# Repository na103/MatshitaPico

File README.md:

<!--
  MatshitaPico — Solid-state CD-ROM drive replacement for the Commodore CDTV
  Copyright (c) 2026 Nicola Avanzi (na103)
  Licensed under Creative Commons Attribution 4.0 International (CC BY 4.0).
  See LICENSE.
-->

# MatshitaPico — a solid-state CD-ROM drive for the Commodore CDTV

**MatshitaPico** is a solid-state replacement for the optical CD-ROM drive of the
**Commodore CDTV**: BIN/CUE disc images stored on a microSD
card take the place of the optical mechanism.

**Why:** many CDTV drives have a worn-out laser and cannot be repaired, and no drop-in
replacement has ever existed. This project keeps these machines alive.

> This repository contains the **CPLD design (HDL)**, **technical documentation**, **RP2350 firmware**, **KiCad hardware project of beta board** and the **Amiga-side `mpdisk.device` + boot CD builder** for hardfiles.
---

## Community beta

Because of the limited turnout in the project's closed beta testing, I have decided to open
MatshitaPico testing up to the whole Amiga community.

The final version should not differ much from this first one, apart from an ATF1508 CPLD in a
TQFP-100 package, programmable in-circuit through a JTAG connector. The key point for the final
version is the **PCB layout**: it must be designed together with a 3D-printed mounting bracket.
The original eject button could also be reused as a control button.

This first version **is** installable — as you can see from the photos [here](https://github.com/na103/MatshitaPico/tree/main/img/beta_assembly) —
but several modifications are needed to fit it. When I laid out the PCB I did not worry about
its dimensions.

## The key insight

The CDTV service manual contains **no schematic for the CD-ROM subsystem**: all of the
CD-ROM electronics (CD-DSP, the Sanyo **LC8951** decoder, the drive's own microcontroller)
live on a PCB **inside the drive mechanism**, not on the motherboard. The motherboard only
carries the *host side* — the **DMAC (U36)**, the **6525/TPI (U32)** and glue logic — which
talks to the drive through connector **CN9** (42 pins, sheet 10 of schematic #252605).

→ **CN9 is the emulation point.** The device plugs into CN9 and pretends to be the entire
drive. The LC8951 does **not** interpret commands (it is a host↔µC FIFO mailbox); the
replacement emulates both the LC8951 host interface and the drive µC command protocol
(the proprietary CDTV/Sony command set).

## Hardware architecture

```
   CDTV (CN9, 5 V TTL)
        |  DB0-7, _HWR/_HRD/_CMD/_STEN/_DTEN/DRQ/_ENABLE/_STCH + RESET
        v
   CPLD  ATF1508AS  (5 V, 128 macrocells, PLCC84, JTAG; socketed, programmed out of circuit)
        |  - real-time 5 V front-end; host-interface FSM (DRQ mode)
        |  - clock division C16M -> BCLK/LRCK; SCOR / subcode generation
        |  <- level shifting 5 V <-> 3.3 V (SN74CBTD16211 bus switch, no DIR, 5 V clamp)
        v
   MCU  RP2350 / Raspberry Pi Pico 2  (3.3 V)
        - drive command protocol - BIN/CUE from SD
        - I2S audio 44.1 kHz (PIO) - subcode Q - UI (NEXT + LED)
   + 16.9344 MHz crystal oscillator (C16M, DIP14 metal-can 5 V TTL)
```

**Key constraint:** the CN9 bus is 5 V TTL and the RP2350 is **not** 5 V-tolerant, so a
native 5 V front-end is required (**ATF1508AS**, the `AS` variant, not `ASV`). The CPLD
performs four things in parallel — master clock, I2S audio, subcode, host DMA — plus command
glue logic; the heavy protocol logic runs on the RP2350.

## What the CPLD does

The CPLD is the only chip that faces CN9 (a pure 5 V domain). It contains:

- **`clkgen`** — derives the audio clocks (`BCLK`, `LRCK`, frame sync) from the `C16M`
  master clock (16.9344 MHz = 384 x 44.1 kHz), so the audio stays phase-coherent with the
  motherboard DAC (Sanyo LC7883M).
- **`host_if`** — the LC8951-style host-interface FSM: it captures host commands (async latch
  on the rising edge of `_HWR`), drives status replies over `_HRD`/`_STEN`, and runs the DMA
  data path in **DRQ mode** (`DRQ` high = byte ready). `EOP` is not on CN9 — the DMAC counts
  it — so ending a sector is just lowering `DRQ`.
- **top level** — subcode generation (`SBCP`/`SCOR`/`EFFK`; `SCCK` is a host **input**) and
  buffering of `DATA`/`EMPHASIS` from the RP2350.

## The golden reference

`cdtv.cpp` from WinUAE (plus `cdtvcr.cpp` for the CDTV-CR variant) is a complete emulation of
the DMAC + 6525 + LC8951 + command protocol. It is the **executable specification** the
firmware is ported from. (The WinUAE sources are not redistributed here — see the WinUAE
project.) The CDTV extended ROM is the real host-side protocol engine.

## Drive command set (summary)

`0x01` seek · `0x02` read · `0x04`/`0x05` motor on/off · `0x09`/`0x0a` play LSN/MSF ·
`0x0b` play track range · `0x82` clear-error · `0x84` mode set · `0x85` mode sense ·
`0x86` capacity · `0x87` subq · `0x8a` read TOC · `0xa2`/`0xa3` front panel.

The full, byte-level command reference — including the vendor `0x6x` hardfile page — is in
[`docs/drive-commands.md`](docs/drive-commands.md).

## Status

The device is functionally complete on real hardware: data boot, persistent disc change,
CD audio (play / pause / skip / stop), CD+G graphics, and the activity LED all work on a real
CDTV. 

## Optional: hardfiles (`mpdisk.device`)

With the firmware built with `ENABLE_MPDISK`, `.hdf` hard-disk images in the root of the SD
card become read/write Amiga units **MPD0..MPD3**, served through the CD controller itself
(no extra hardware). A small boot CD loads `mpdisk.device`, mounts the hardfiles and hands the
system over to MPD0:, so a CDTV can run Workbench from a writable disk. The Amiga sources and
the boot CD builder are in [`amiga/`](amiga) and [`tools/`](tools) — see
[`amiga/README.md`](amiga/README.md).

## Thanks
Thankyou to all the people who have support this project.<br>
Andrea Quagliarini, Mirco Gaggiottini, Carlo Santagostino, Federico Di Dato.

## License

This work is licensed under the **Creative Commons Attribution 4.0 International License
(CC BY 4.0)**. See [`LICENSE`](LICENSE). You are free to share and adapt the material for any
purpose, provided you give appropriate credit.

<br><br>
If you found this my work useful, please consider buying me a cup of coffee if you want:<br>

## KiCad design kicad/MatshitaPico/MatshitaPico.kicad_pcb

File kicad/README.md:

## Bill of materials
| Qt. |    Description     |             Designator          |    Part code       |             Note              |
|:---:|--------------------|---------------------------------|--------------------|-------------------------------|
|4    |Res 10K             |R1-R3,R22                        |RC1206FR-0710KL
|6    |Res 100R            |R15,R17-R21                      |RC1206FR-07100RL    |                               |
|8    |Res 47K             |R4-R11                           |RC1206FR-0747KL     |                               |
|2    |Res 470R            |R12, R13                         |RC1206FR-07470RL    |                               |
|2    |Res 1K              |R14,R16                          |RC1206FR-071KL      |                               |
|1    |Res 0R              |R23                              |RC1206FR-070RL      |                               |
|1    |Bus Array 8RES 2.2K |RN1                              |4609X-101-222LF     |                               |
|1    |Bus Array 4RES 1K   |RN2                              |4605X-101-102LF     |                               |
|17   |Cap 100nF           |C1-C13,C17-C20                   |C1206C104K5RACTU    |                               |
|2    |Cap 10uF            |C15,C16                          |EEA-GA1V100H        |                               |
|1    |Cap 47uF            |C14                              |EEU-FC1V470H        |                               |
|1    |DIODE SCHOTTKY      |D1                               |MBR120ESFT3G        |                               |
|1    |DIODE SCHOTTKY      |D2                               |BAT54W-E3-08        |                               |
|1    |BUS SWITCH          |U2                               |SN74CBTD16211DGGR   |                               |
|1    |CPLD ATF1508        |U1                               |ATF1508AS-10JU84    | from ebay or utsource.net     |
|1    |OSC DIP 16.9344MHZ  |Y1                               |NA                  | from aliexpress               | 
|1    |74LS245             |U3                               |SN74LS245DWR        |                               |
|2    |74LS244             |U4,U6                            |SN74LS244DWR        |                               |
|1    |74LS541             |U5                               |SN74LS541DWR        |                               | 
|1    |SOCKET PLCC 84POS   |U1                               |940-44-084-24-000000|                               |
|1    |PI PICO 2 RP2350    |A1                               |SC1631              |                               |
|1    |CONN 4POS 5.08MM    |J1                               |641737-1            |                               |
|1    |CONN 40POS 2.54MM   |J2                               |61204021721         |                               |
|1    |CONN 3POS 2MM       |J3                               |S3B-PH-K-S          |                               |
|1    |CONN SD CARD SMD    |SD1                              |10067847-011RLF     |                               |
|1    |SWITCH SPST-NO      |SW1                              |2-1825027-0         |                               |

## Note ##
The ATF150x programmer needed to program the CPLD can be found [here](https://github.com/roscopeco/atfprog-hardware).

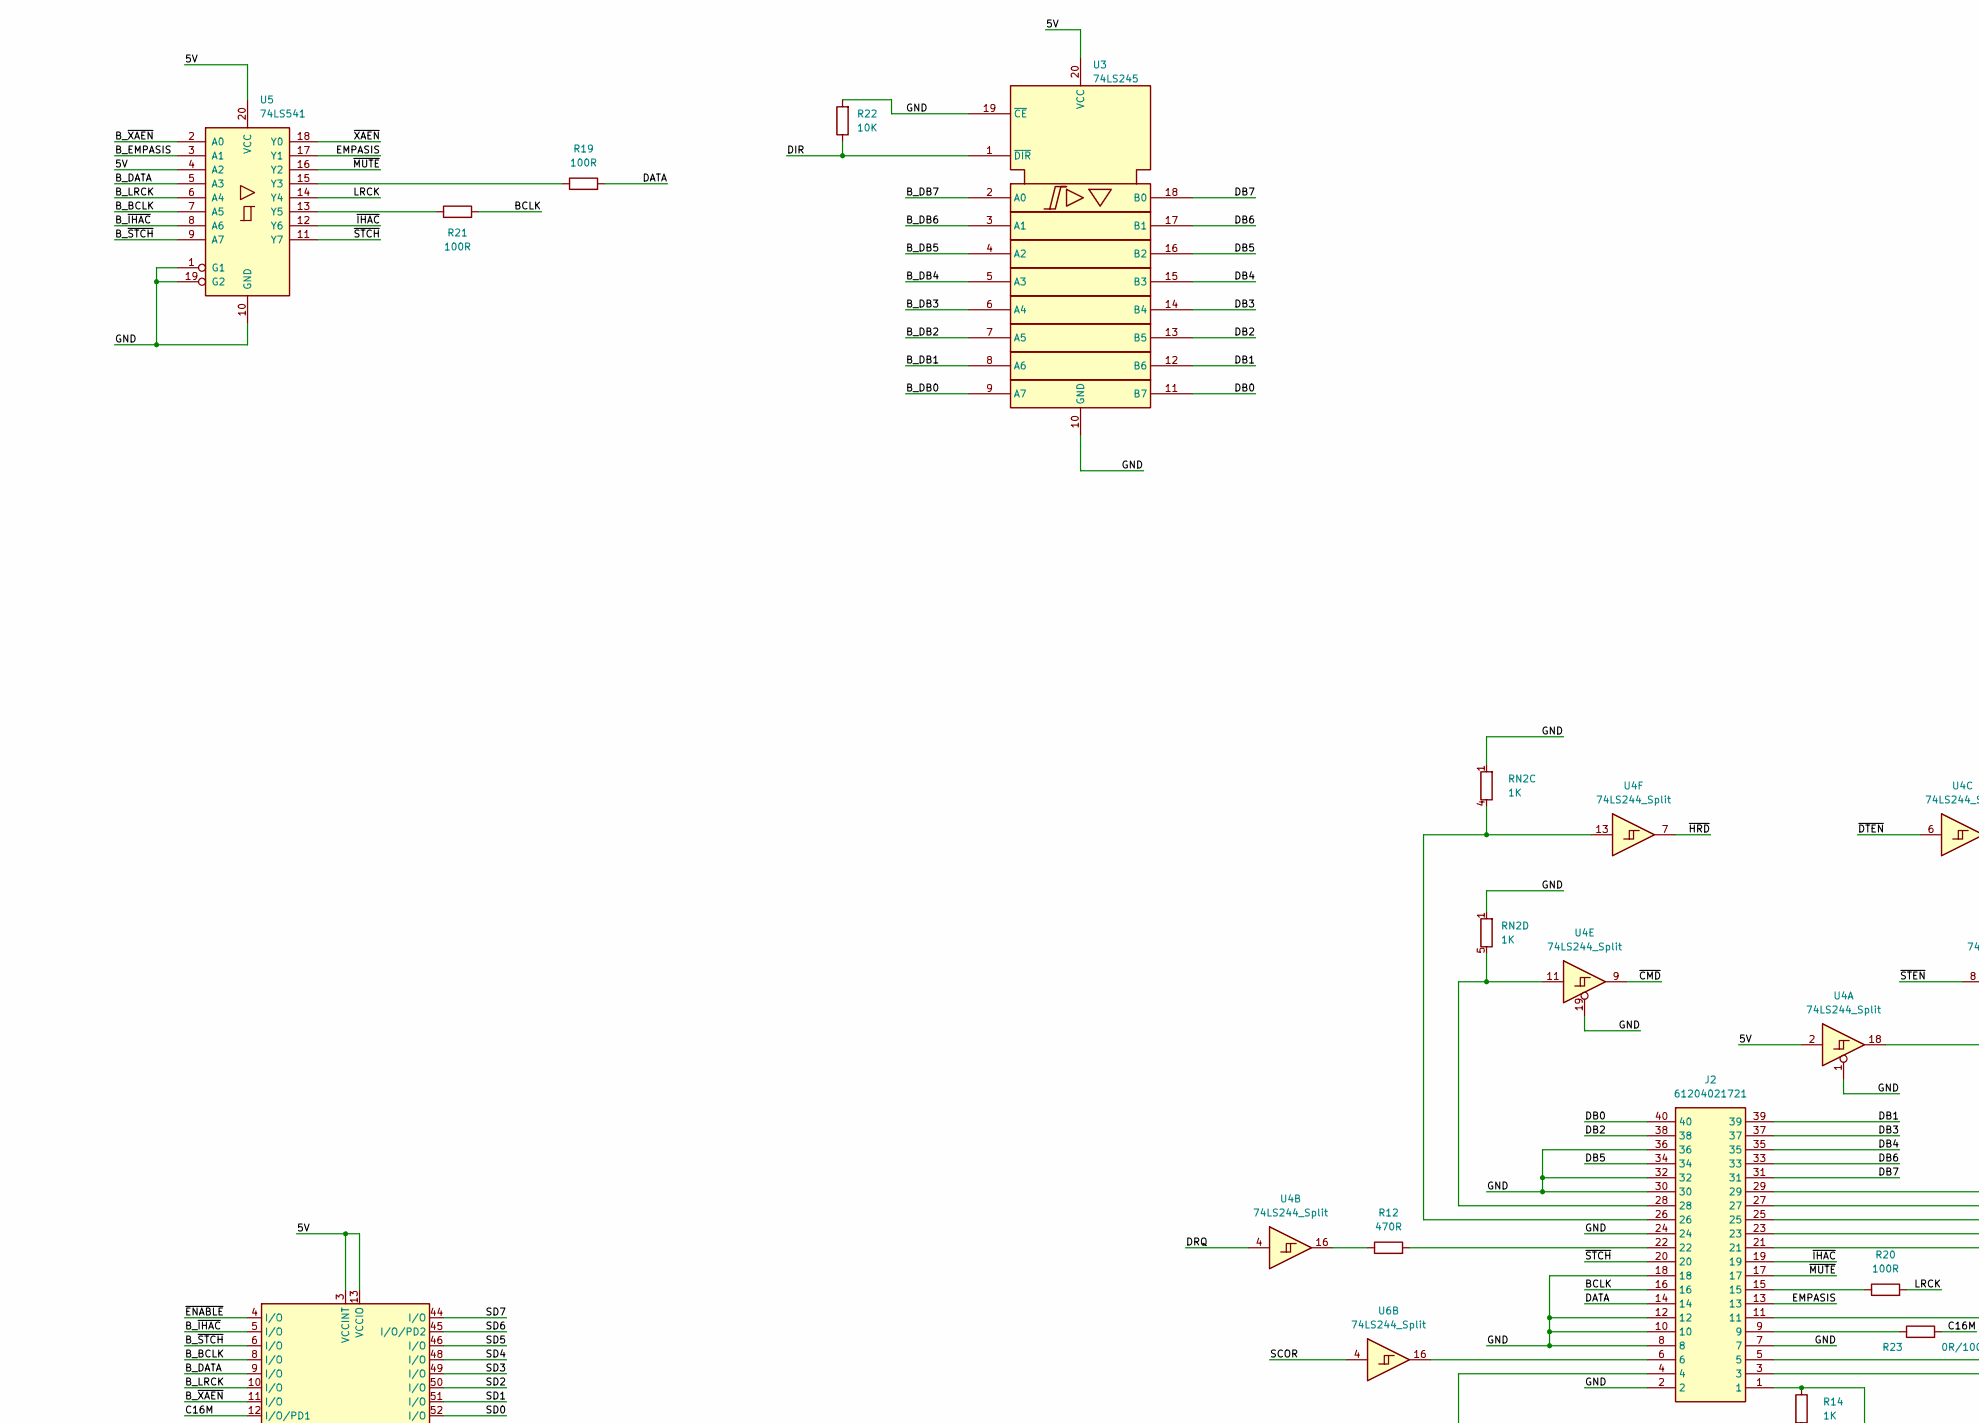
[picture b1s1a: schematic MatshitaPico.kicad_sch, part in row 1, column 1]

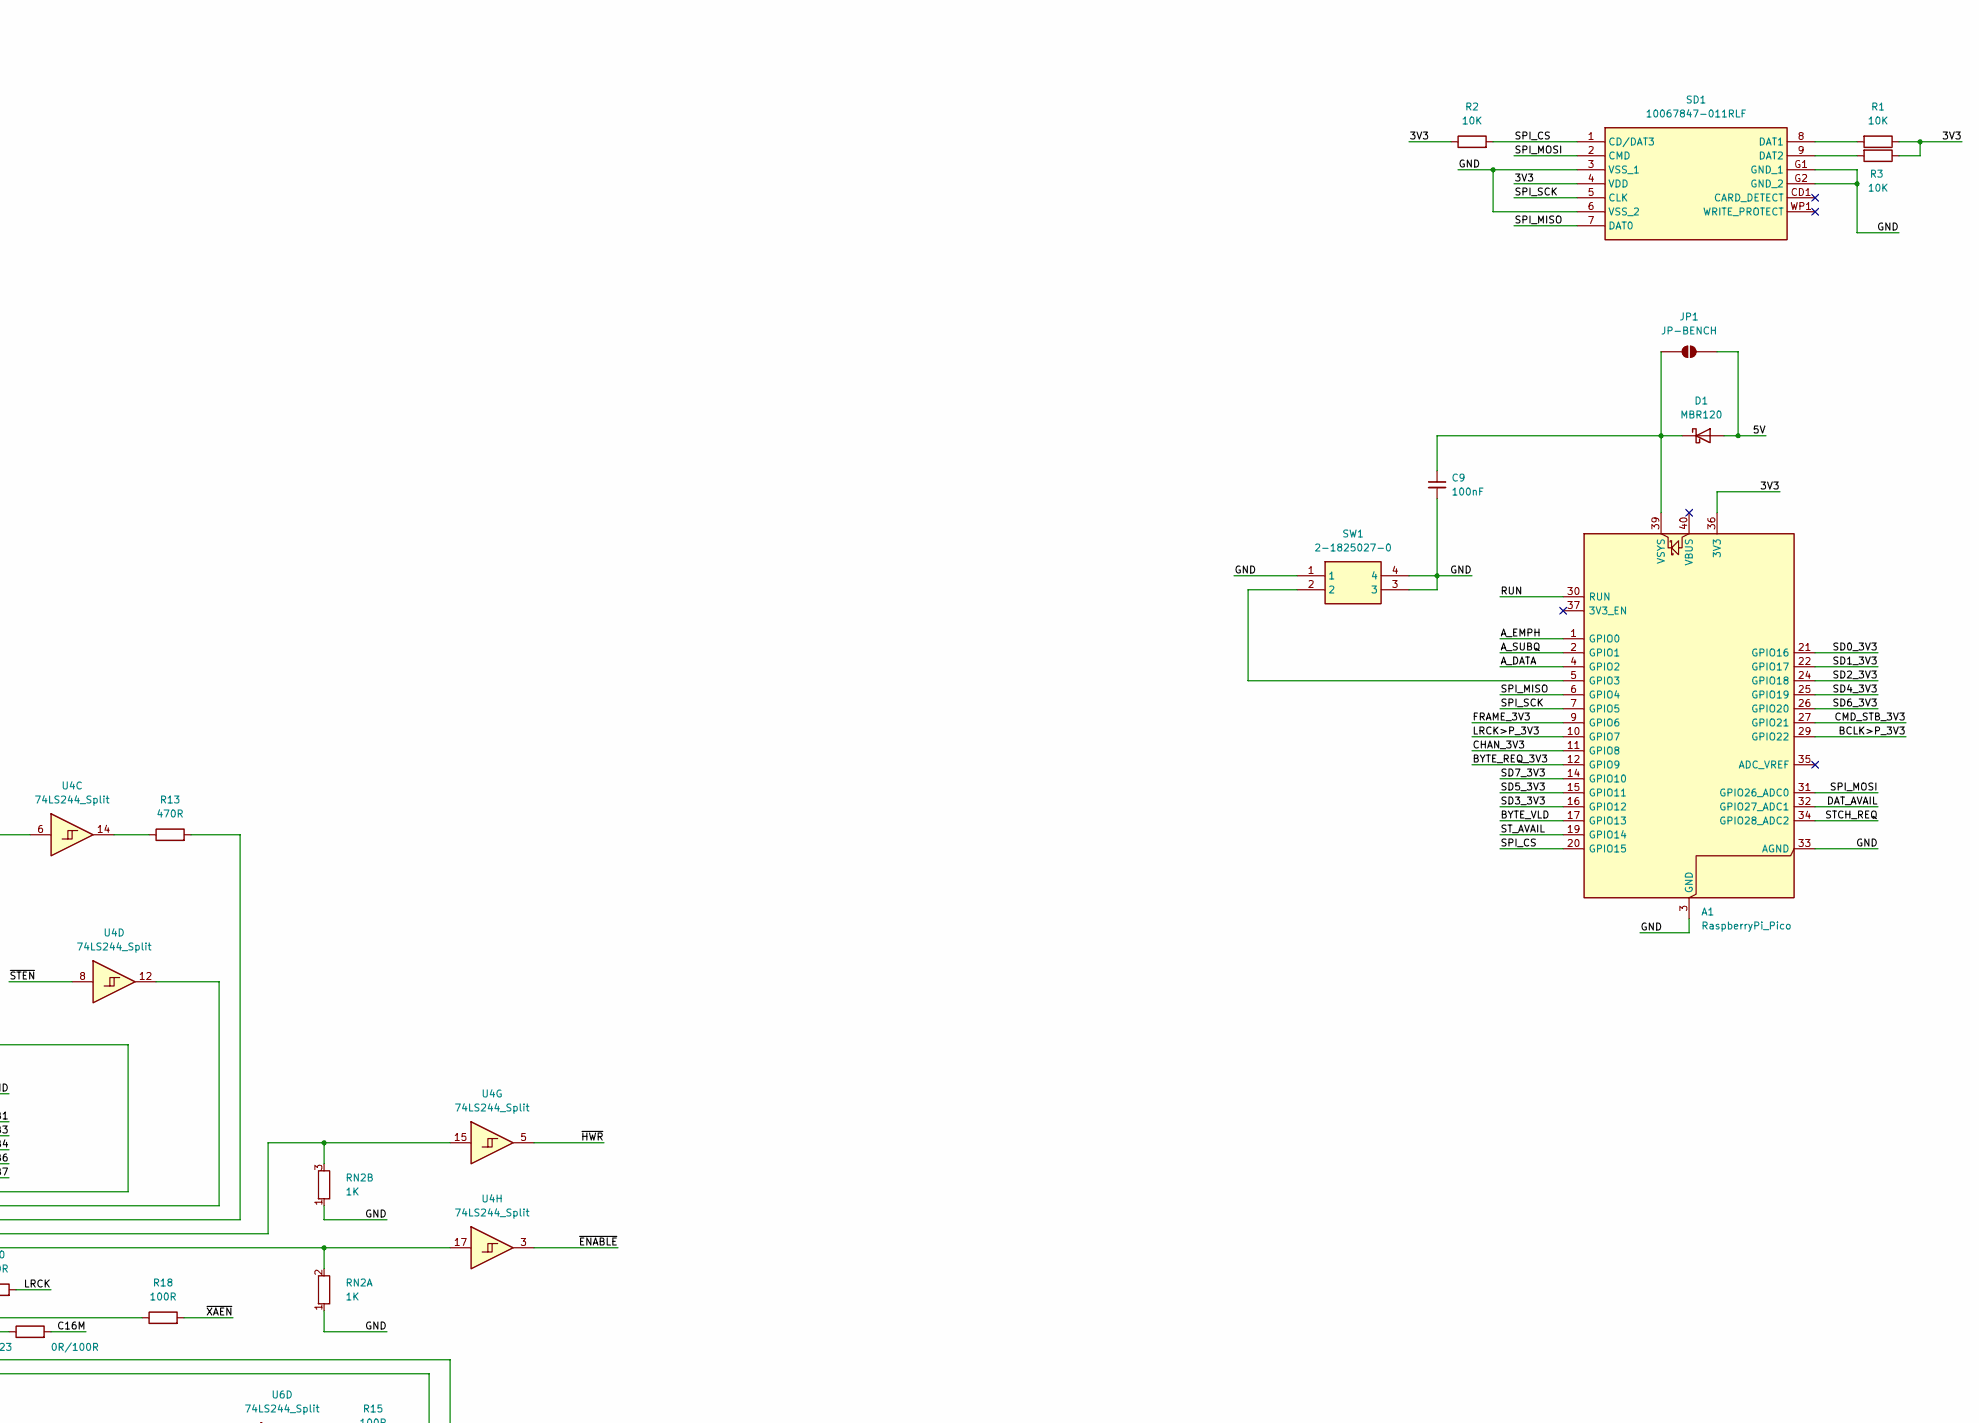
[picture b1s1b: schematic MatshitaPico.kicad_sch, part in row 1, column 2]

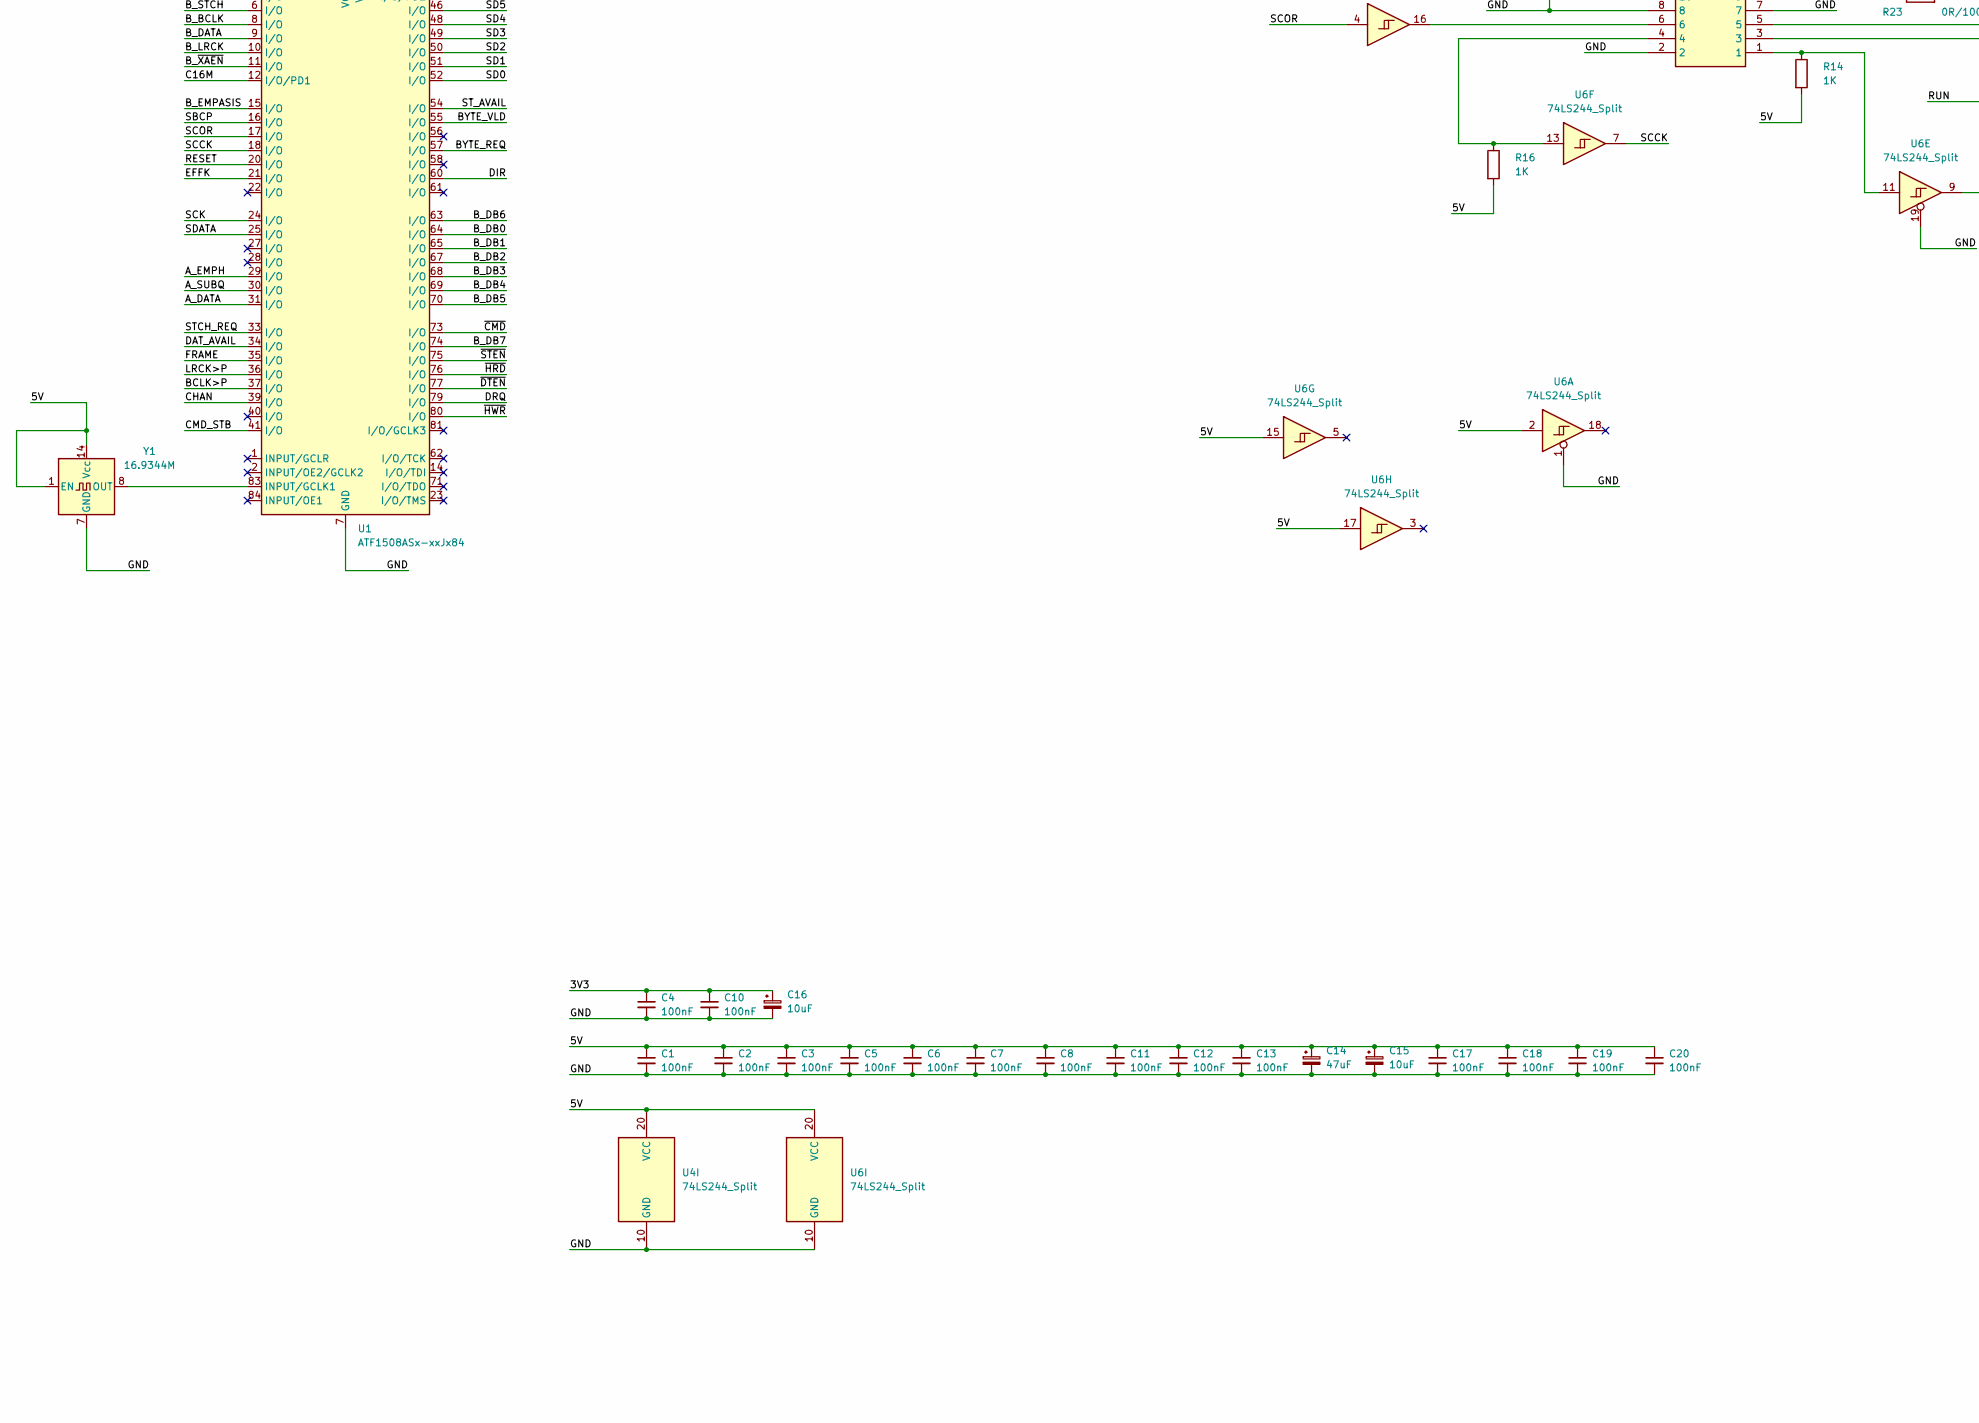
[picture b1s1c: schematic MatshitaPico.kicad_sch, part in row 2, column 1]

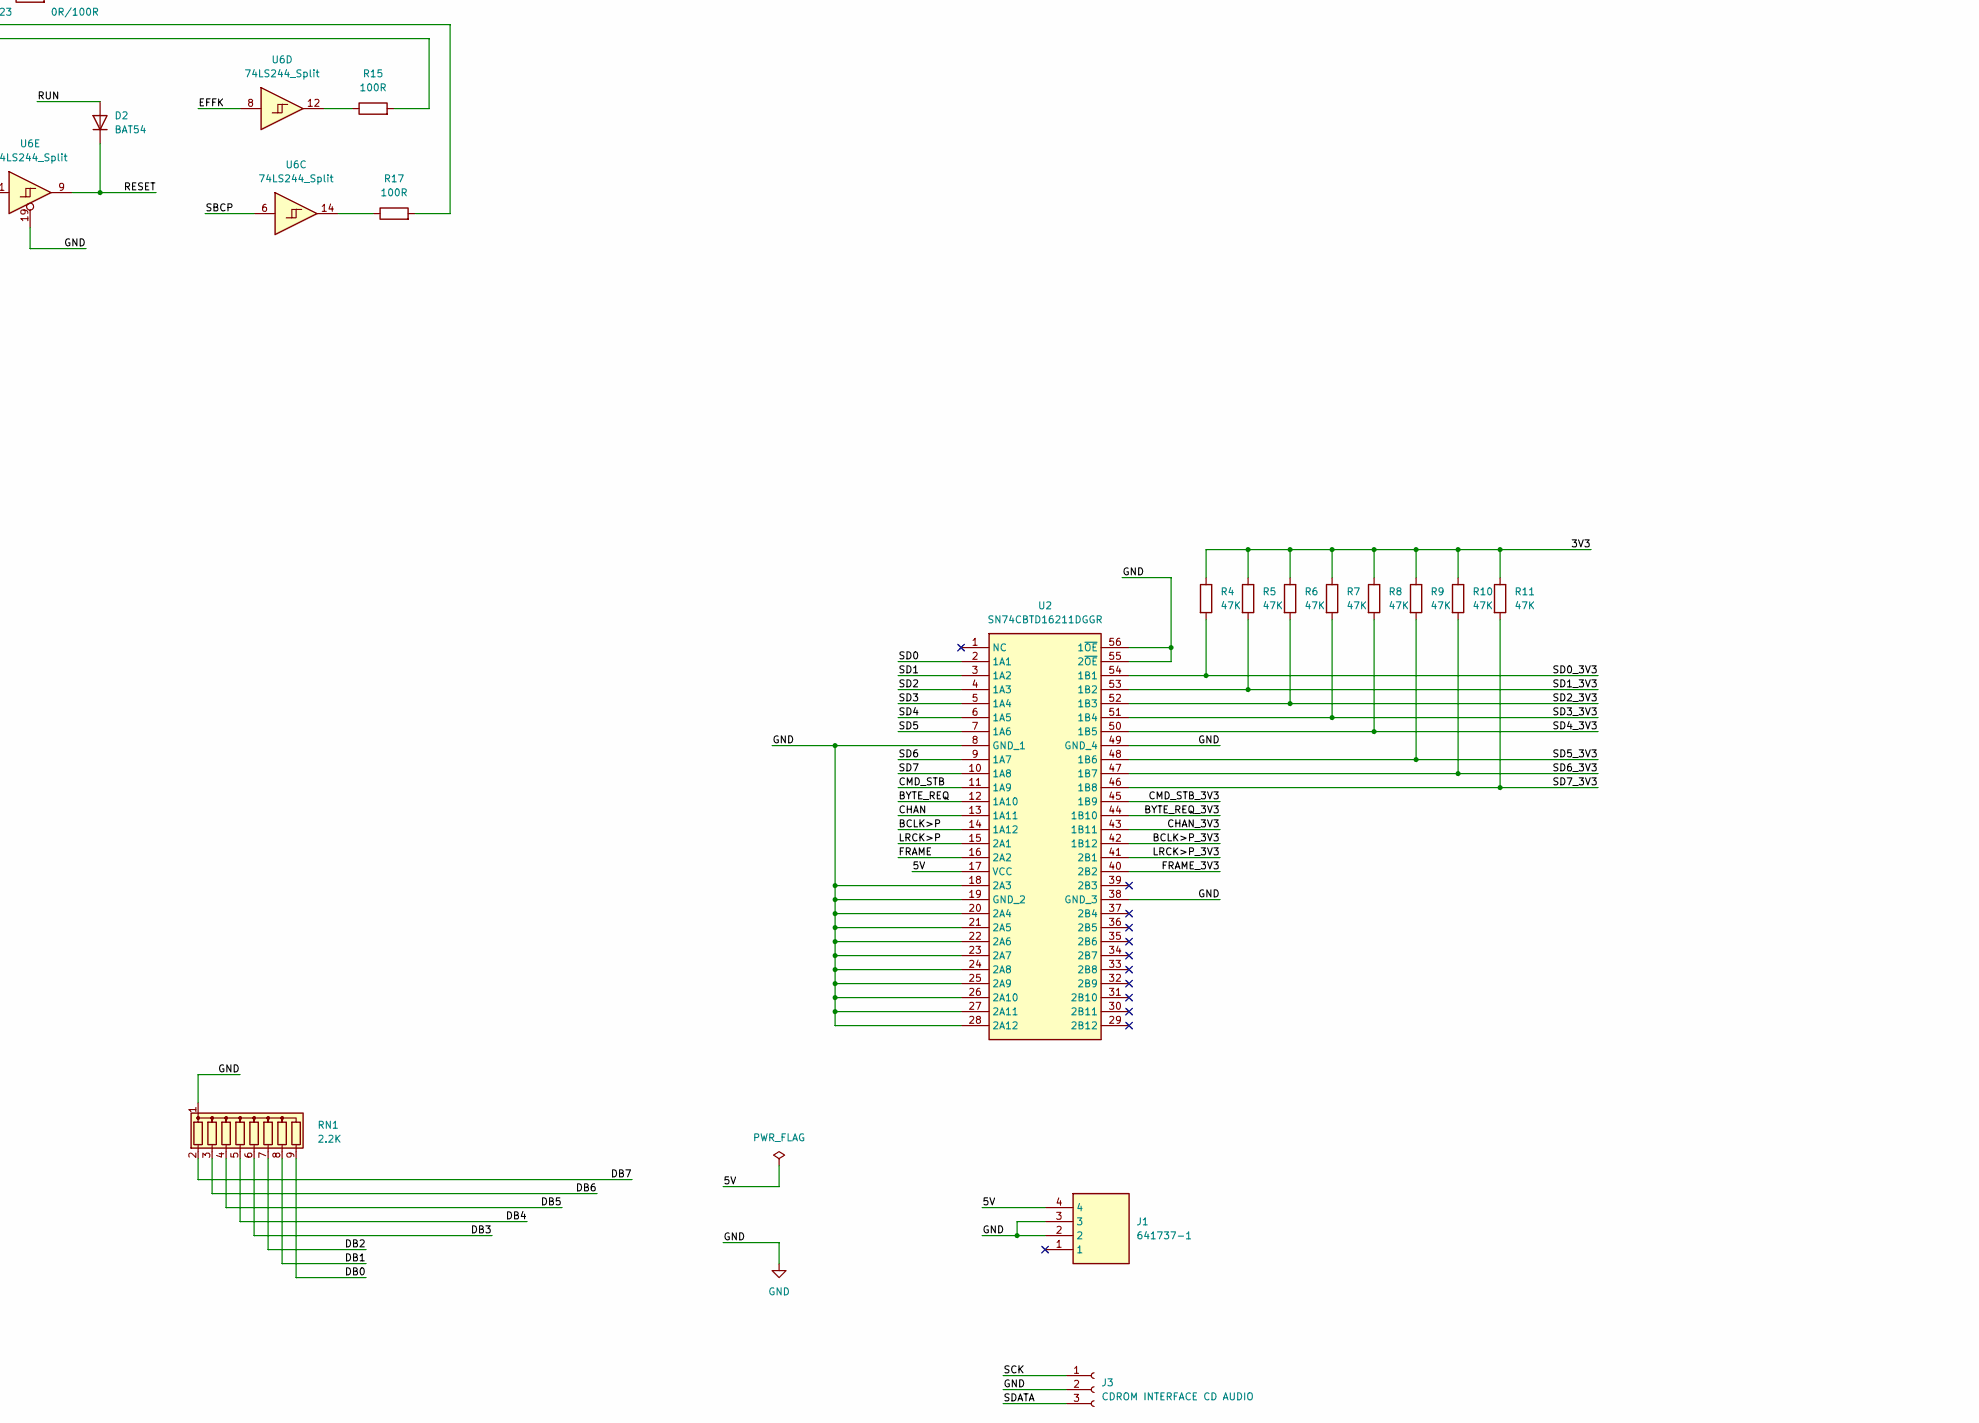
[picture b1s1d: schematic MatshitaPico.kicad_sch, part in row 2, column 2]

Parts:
A1: RaspberryPi_Pico; RaspberryPi_Pico_Common_no_wifi
C1, C2, C3, C4, C5, C6, C7, C8, C9, C10, C11, C12, C13, C17, C18, C19, C20: 100nF; C_1206_3216Metric_Pad1.33x1.80mm_HandSolder
C14: 47uF; CP_Radial_D5.0mm_P2.50mm
C15, C16: 10uF; CP_Radial_D5.0mm_P2.50mm
D1: MBR120; SODFL3616X98N
D2: BAT54; SODFL3616X98N
J1: 641737-1; Mouser Part Number 571-6417371
J2: 61204021721; Mouser Part Number 710-61204021721
J3: CDROM INTERFACE CD AUDIO; JST_PH_S3B-PH-K_1x03_P2.00mm_Horizontal
JP1: JP-BENCH; SolderJumper-2_P1.3mm_Open_RoundedPad1.0x1.5mm
R1, R2, R3, R22: 10K; R_1206_3216Metric_Pad1.30x1.75mm_HandSolder
R4, R5, R6, R7, R8, R9, R10, R11: 47K; R_1206_3216Metric_Pad1.30x1.75mm_HandSolder
R12, R13: 470R; R_1206_3216Metric_Pad1.30x1.75mm_HandSolder
R14, R16: 1K; R_1206_3216Metric_Pad1.30x1.75mm_HandSolder
R15, R17, R18, R19, R20, R21: 100R; R_1206_3216Metric_Pad1.30x1.75mm_HandSolder
R23: 0R/100R; R_1206_3216Metric_Pad1.30x1.75mm_HandSolder
RN1: 2.2K; R_Array_SIP9
RN2: 1K; R_Array_SIP5
SD1: 10067847-011RLF; 10067847011RLF; Mouser Part Number 649-10067847-011RLF
SW1: 2-1825027-0; 218250270; Mouser Part Number 506-2-1825027-0
U1: ATF1508ASx-xxJx84; PLCC-84_THT-Socket
U2: SN74CBTD16211DGGR; SOP50P810X120-56N; Mouser Part Number 595-74CBTD16211DGGR
U3: 74LS245; SOIC-20W_7.5x12.8mm_P1.27mm
U4, U6: 74LS244_Split; SOIC-20W_7.5x12.8mm_P1.27mm
U5: 74LS541; SOIC-20W_7.5x12.8mm_P1.27mm
Y1: 16.9344M; Oscillator_DIP-14

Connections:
/3V3: A1.36 (3V3), C4.1, C10.1, C16.1, R1.1, R2.1, R3.1, R4.1, R5.1, R6.1, R7.1, R8.1, R9.1, R10.1, R11.1, SD1.4 (VDD)
/5V: C1.1, C2.1, C3.1, C5.1, C6.1, C7.1, C8.1, C11.1, C12.1, C13.1, C14.1, C15.1, C17.1, C18.1, C19.1, C20.1, D1.2 (A), J1.4, JP1.2 (B), R14.2, R16.2, U1.3 (VCCINT), U1.13 (VCCIO), U1.26 (VCCIO), U1.38 (VCCIO), U1.43 (VCCINT), U1.53 (VCCIO), U1.66 (VCCIO), U1.78 (VCCIO), U2.17 (VCC), U3.20 (VCC), U4.2, U4.20 (VCC), U5.4 (A2), U5.20 (VCC), U6.2, U6.15, U6.17, U6.20 (VCC), Y1.1 (EN), Y1.14 (Vcc)
/A_DATA: A1.4 (GPIO2), U1.31 (I/O)
/A_EMPH: A1.1 (GPIO0), U1.29 (I/O)
/A_SUBQ: A1.2 (GPIO1), U1.30 (I/O)
/BCLK: J2.16, R21.2
/BCLK>P: U1.37 (I/O), U2.14 (1A12)
/BCLK>P_3V3: A1.29 (GPIO22), U2.42 (1B12)
/BYTE_REQ: U1.57 (I/O), U2.12 (1A10)
/BYTE_REQ_3V3: A1.12 (GPIO9), U2.44 (1B10)
/BYTE_VLD: A1.17 (GPIO13), U1.55 (I/O)
/B_BCLK: U1.8 (I/O), U5.7 (A5)
/B_DATA: U1.9 (I/O), U5.5 (A3)
/B_DB0: U1.64 (I/O), U3.9 (A7)
/B_DB1: U1.65 (I/O), U3.8 (A6)
/B_DB2: U1.67 (I/O), U3.7 (A5)
/B_DB3: U1.68 (I/O), U3.6 (A4)
/B_DB4: U1.69 (I/O), U3.5 (A3)
/B_DB5: U1.70 (I/O), U3.4 (A2)
/B_DB6: U1.63 (I/O), U3.3 (A1)
/B_DB7: U1.74 (I/O), U3.2 (A0)
/B_EMPASIS: U1.15 (I/O), U5.3 (A1)
/B_LRCK: U1.10 (I/O), U5.6 (A4)
/B_~IHAC: U1.5 (I/O), U5.8 (A6)
/B_~STCH: U1.6 (I/O), U5.9 (A7)
/B_~XAEN: U1.11 (I/O), U5.2 (A0)
/C16M: R23.2, U1.12 (I/O/PD1)
/CHAN: U1.39 (I/O), U2.13 (1A11)
/CHAN_3V3: A1.11 (GPIO8), U2.43 (1B11)
/CMD_STB: U1.41 (I/O), U2.11 (1A9)
/CMD_STB_3V3: A1.27 (GPIO21), U2.45 (1B9)
/DATA: J2.14, R19.2
/DAT_AVAIL: A1.32 (GPIO27_ADC1), U1.34 (I/O)
/DB0: J2.40, RN1.9 (R8), U3.11 (B7)
/DB1: J2.39, RN1.8 (R7), U3.12 (B6)
/DB2: J2.38, RN1.7 (R6), U3.13 (B5)
/DB3: J2.37, RN1.6 (R5), U3.14 (B4)
/DB4: J2.35, RN1.5 (R4), U3.15 (B3)
/DB5: J2.34, RN1.4 (R3), U3.16 (B2)
/DB6: J2.33, RN1.3 (R2), U3.17 (B1)
/DB7: J2.31, RN1.2 (R1), U3.18 (B0)
/DIR: R22.1, U1.60 (I/O), U3.1 (~DIR)
/DRQ: U1.79 (I/O), U4.4
/EFFK: U1.21 (I/O), U6.8
/EMPASIS: J2.13, U5.17 (Y1)
/FRAME: U1.35 (I/O), U2.16 (2A2)
/FRAME_3V3: A1.9 (GPIO6), U2.40 (2B2)
/LRCK: R20.2, U5.14 (Y4)
/LRCK>P: U1.36 (I/O), U2.15 (2A1)
/LRCK>P_3V3: A1.10 (GPIO7), U2.41 (2B1)
/RESET: D2.1 (K), U1.20 (I/O), U6.9
/RUN: A1.30 (RUN), D2.2 (A)
/SBCP: U1.16 (I/O), U6.6
/SCCK: U1.18 (I/O), U6.7
/SCK: J3.1, U1.24 (I/O)
/SCOR: U1.17 (I/O), U6.4
/SD0: U1.52 (I/O), U2.2 (1A1)
/SD0_3V3: A1.21 (GPIO16), R4.2, U2.54 (1B1)
/SD1: U1.51 (I/O), U2.3 (1A2)
/SD1_3V3: A1.22 (GPIO17), R5.2, U2.53 (1B2)
/SD2: U1.50 (I/O), U2.4 (1A3)
/SD2_3V3: A1.24 (GPIO18), R6.2, U2.52 (1B3)
/SD3: U1.49 (I/O), U2.5 (1A4)
/SD3_3V3: A1.16 (GPIO12), R7.2, U2.51 (1B4)
/SD4: U1.48 (I/O), U2.6 (1A5)
/SD4_3V3: A1.25 (GPIO19), R8.2, U2.50 (1B5)
/SD5: U1.46 (I/O), U2.7 (1A6)
/SD5_3V3: A1.15 (GPIO11), R9.2, U2.48 (1B6)
/SD6: U1.45 (I/O/PD2), U2.9 (1A7)
/SD6_3V3: A1.26 (GPIO20), R10.2, U2.47 (1B7)
/SD7: U1.44 (I/O), U2.10 (1A8)
/SD7_3V3: A1.14 (GPIO10), R11.2, U2.46 (1B8)
/SDATA: J3.3, U1.25 (I/O)
/SPI_CS: A1.20 (GPIO15), R2.2, SD1.1 (CD/DAT3)
/SPI_MISO: A1.6 (GPIO4), SD1.7 (DAT0)
/SPI_MOSI: A1.31 (GPIO26_ADC0), SD1.2 (CMD)
/SPI_SCK: A1.7 (GPIO5), SD1.5 (CLK)
/STCH_REQ: A1.34 (GPIO28_ADC2), U1.33 (I/O)
/ST_AVAIL: A1.19 (GPIO14), U1.54 (I/O)
/~CMD: U1.73 (I/O), U4.9
/~DTEN: U1.77 (I/O), U4.6
/~ENABLE: U1.4 (I/O), U4.3
/~HRD: U1.76 (I/O), U4.7
/~HWR: U1.80 (I/O), U4.5
/~IHAC: J2.19, U5.12 (Y6)
/~MUTE: J2.17, U5.16 (Y2)
/~STCH: J2.20, U5.11 (Y7)
/~STEN: U1.75 (I/O), U4.8
/~XAEN: R18.2, U5.18 (Y0)
GND: A1.3 (GND), A1.8 (GND), A1.13 (GND), A1.18 (GND), A1.23 (GND), A1.28 (GND), A1.33 (AGND), A1.38 (GND), C1.2, C2.2, C3.2, C4.2, C5.2, C6.2, C7.2, C8.2, C9.2, C10.2, C11.2, C12.2, C13.2, C14.2, C15.2, C16.2, C17.2, C18.2, C19.2, C20.2, J1.2, J1.3, J2.2, J2.7, J2.8, J2.10, J2.12, J2.18, J2.24, J2.30, J2.32, J2.36, J3.2, R22.2, RN1.1 (common), RN2.1 (R1), SD1.3 (VSS_1), SD1.6 (VSS_2), SD1.G1 (GND_1), SD1.G2 (GND_2), SW1.1, SW1.3, SW1.4, U1.7 (GND), U1.19 (GND), U1.32 (GND), U1.42 (GND), U1.47 (GND), U1.59 (GND), U1.72 (GND), U1.82 (GND), U2.8 (GND_1), U2.18 (2A3), U2.19 (GND_2), U2.20 (2A4), U2.21 (2A5), U2.22 (2A6), U2.23 (2A7), U2.24 (2A8), U2.25 (2A9), U2.26 (2A10), U2.27 (2A11), U2.28 (2A12), U2.38 (GND_3), U2.49 (GND_4), U2.55 (2~OE), U2.56 (1~OE), U3.10 (GND), U3.19 (~CE), U4.1, U4.10 (GND), U4.19, U5.1 (G1), U5.10 (GND), U5.19 (G2), U6.1, U6.10 (GND), U6.19, Y1.7 (GND)
unnamed: A1.5 (GPIO3), SW1.2
unnamed: A1.39 (VSYS), C9.1, D1.1 (K), JP1.1 (A)
unnamed: J2.1, R14.1, U6.11
unnamed: J2.3, R15.2
unnamed: J2.4, R16.1, U6.13
unnamed: J2.5, R17.2
unnamed: J2.6, U6.16
unnamed: J2.9, R23.1
unnamed: J2.11, R18.1
unnamed: J2.15, R20.1
unnamed: J2.22, R12.2
unnamed: J2.25, R13.2
unnamed: J2.27, U4.12
unnamed: J2.29, U4.18
unnamed: R12.1, U4.16
unnamed: R13.1, U4.14
unnamed: R15.1, U6.12
unnamed: R17.1, U6.14
unnamed: J2.21, RN2.2 (R1.2), U4.17
unnamed: J2.23, RN2.3 (R2.2), U4.15
unnamed: J2.26, RN2.4 (R3.2), U4.13
unnamed: J2.28, RN2.5 (R4.2), U4.11
unnamed: R1.2, SD1.8 (DAT1)
unnamed: R3.2, SD1.9 (DAT2)
unnamed: U1.83 (INPUT/GCLK1), Y1.8 (OUT)
unnamed: R19.1, U5.15 (Y3)
unnamed: R21.1, U5.13 (Y5)

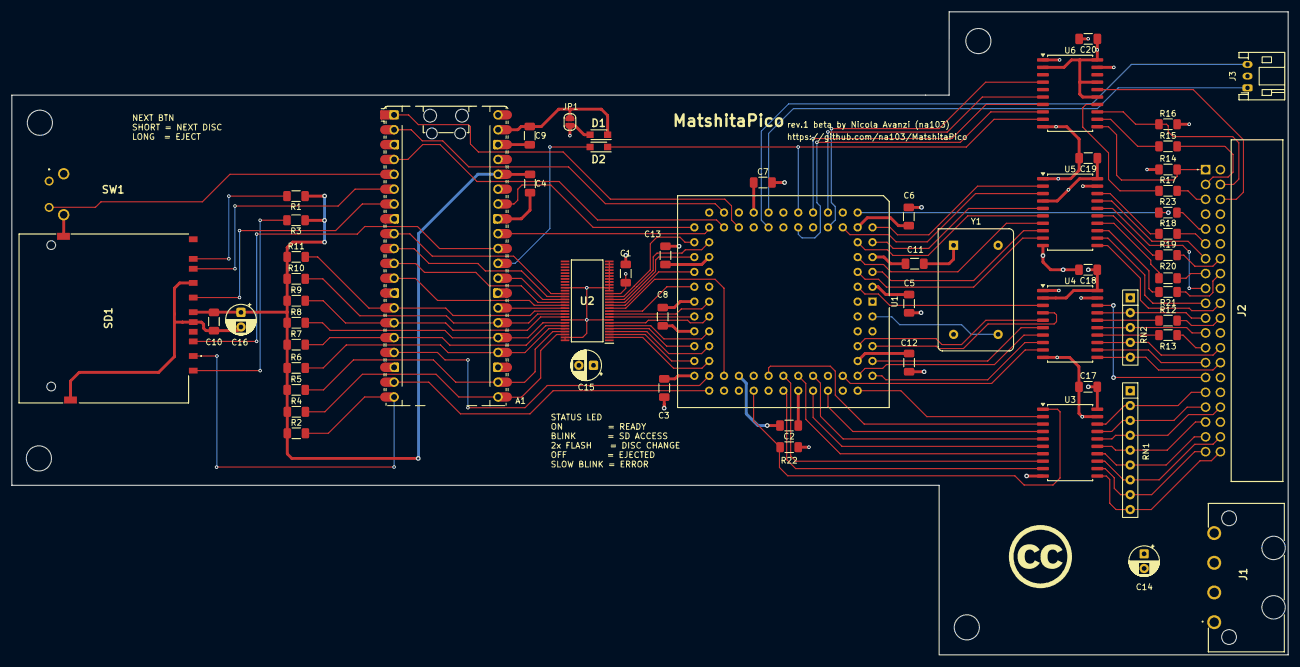
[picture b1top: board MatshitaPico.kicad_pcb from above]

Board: 4 copper layers, 218.3 x 110.0 mm, 61 parts (0 on the bottom side), 117 nets.

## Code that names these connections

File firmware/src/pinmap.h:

// =============================================================================
// MatshitaPico -- Solid-state CD-ROM drive replacement for the Commodore CDTV
// Copyright (c) 2026 Nicola Avanzi (na103)
// Licensed under Creative Commons Attribution 4.0 International (CC BY 4.0).
// See LICENSE.
// =============================================================================
// pinmap.h -- RP2350 / Pico 2 (A1) GPIO assignment.
// This is extracted from the KiCad schematic and is the hardware truth: the PCB
// is already routed on these pins. Do NOT change them without re-routing the PCB.
// Budget: 26/26 GPIO used (GP0-GP22 + GP26/27/28); GP23/24/25 are module-internal,
// GP25 = onboard status LED.
//
// CPLD contract (host_if.v / MatshitaPico_top.v):
//   CPLD -> Pico (via SN74CBTD16211, 5V->3.3V): CMD_STB, BYTE_REQ, CHAN, BCLK, LRCK, FRAME
//   Pico -> CPLD (direct, 3.3V->TTL):           BYTE_VLD, ST_AVAIL, DAT_AVAIL, STCH_REQ,
//                                               A_DATA, A_SUBQ, A_EMPH
//   bidirectional data bus (via shifter):       SD0..SD7
// =============================================================================
#pragma once
#include "pico/stdlib.h"

// ---- Host data bus SD[7:0] (bidirectional, via SN74CBTD16211) ----------------
// NOT contiguous: no PIO on the bus, use gather/scatter (see host_link.cpp). At
// CDTV rates (~6.5 us/byte at 1x) software gather/scatter is more than enough.
static constexpr uint PIN_SD0 = 16;
static constexpr uint PIN_SD1 = 17;
static constexpr uint PIN_SD2 = 18;
static constexpr uint PIN_SD3 = 12;
static constexpr uint PIN_SD4 = 19;
static constexpr uint PIN_SD5 = 11;
static constexpr uint PIN_SD6 = 20;
static constexpr uint PIN_SD7 = 10;
static constexpr uint PIN_SD[8] = {
    PIN_SD0, PIN_SD1, PIN_SD2, PIN_SD3, PIN_SD4, PIN_SD5, PIN_SD6, PIN_SD7
};
// mask of all data-bus bits (for gpio_set_dir_masked / get_all)
static constexpr uint32_t SD_BUS_MASK =
    (1u<<PIN_SD0)|(1u<<PIN_SD1)|(1u<<PIN_SD2)|(1u<<PIN_SD3)|
    (1u<<PIN_SD4)|(1u<<PIN_SD5)|(1u<<PIN_SD6)|(1u<<PIN_SD7);

// ---- Handshake CPLD -> Pico (inputs) -----------------------------------------
static constexpr uint PIN_CMD_STB  = 21;  // pulse: command byte on SD[] from the CPLD
static constexpr uint PIN_BYTE_REQ = 9;   // pulse: "give me the next byte" (status/data)
static constexpr uint PIN_CHAN     = 8;   // 0 = status, 1 = data (which next byte)

// ---- Handshake Pico -> CPLD (outputs) ----------------------------------------
static constexpr uint PIN_BYTE_VLD  = 13;  // valid byte placed on SD[] by the Pico
static constexpr uint PIN_ST_AVAIL  = 14;  // status bytes available -> STEN
static constexpr uint PIN_DAT_AVAIL = 27;  // data transfer ready -> DRQ
static constexpr uint PIN_STCH_REQ  = 28;  // async notification request -> STCH

// ---- Audio clocks from the CPLD (inputs; I2S slave) --------------------------
static constexpr uint PIN_BCLK  = 22;  // bit clock (C16M/8 = 48 fs)
static constexpr uint PIN_LRCK  = 7;   // L/R clock (fs = 44.1 kHz, high = L)
static constexpr uint PIN_FRAME = 6;   // KiCad net "FRAME", reused as SCOR: subcode
                                       // block sync (75 Hz) for the subq_tx PIO
                                       // (I2S aligns on LRCK, no longer needs it)

// ---- Audio / subcode Pico -> CPLD (outputs) ----------------------------------
static constexpr uint PIN_A_DATA = 2;  // serial audio sample (I2S, MSB-first)
static constexpr uint PIN_A_SUBQ = 1;  // subcode Q data stream (the CPLD makes the clocks)
static constexpr uint PIN_A_EMPH = 0;  // de-emphasis flag (per track)

// ---- SD card (3.3V, direct - does NOT pass through the shifter) --------------
// These 4 pins do NOT form any RP2350 hardware SPI; on rev.0 the SD is driven by
// SPI over PIO (pio2 free). See hw_config.c / sd_spi_pio.
static constexpr uint PIN_SD_SCK  = 5;   // CLK   (SD-05)
static constexpr uint PIN_SD_MOSI = 26;  // CMD   (SD-02)
static constexpr uint PIN_SD_MISO = 4;   // DAT0  (SD-07)
static constexpr uint PIN_SD_CS   = 15;  // DAT3  (SD-01)  external 10k pull-up to 3V3

// ---- UI ----------------------------------------------------------------------
static constexpr uint PIN_NEXT_BTN = 3;            // NEXT button -> GND, internal pull-up
static constexpr uint PIN_LED      = PICO_DEFAULT_LED_PIN; // GP25 onboard (status)
